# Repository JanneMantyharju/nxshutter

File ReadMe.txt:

This repository contains sources and schematics for Samsung NX camera remote shutter and rc interface
For more information see: http://wp.me/p12J9M-41

Files in this repository:
shutter/ - Source files, compile with arduino
shutter.sch - Schematics for camera cable
rx_switch.sch - Schematics for rc interface

The pin definitions are for AtTiny2313, change them if you use different type of
controller

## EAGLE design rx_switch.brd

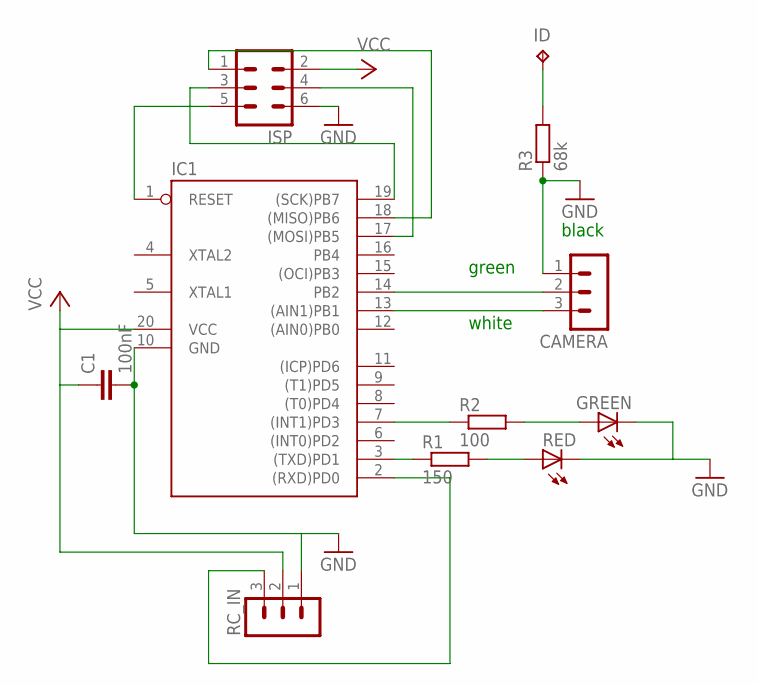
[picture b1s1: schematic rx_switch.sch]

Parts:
C1: 100nF; C0805
CAMERA: MA03-1
GREEN: LED_E; LED_1206
IC1: AT90S2313S; SO20L
ID: TPPAD1-13; P1-13
ISP: MA03-2
R1: 150; R1206
R2: 100; R1206
R3: 68k; R1206
RC_IN: MA03-1
RED: LED_E; LED_1206

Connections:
GND: C1.2, CAMERA.1, GREEN.C, IC1.10 (GND), ISP.6, R3.1, RC_IN.1, RED.C
ISP: IC1.19 ((SCK)PB7), ISP.3
unnamed: IC1.1 (RESET), ISP.5
unnamed: IC1.17 ((MOSI)PB5), ISP.4
unnamed: IC1.2 ((RXD)PD0), RC_IN.3
unnamed: CAMERA.2, IC1.14 (PB2)
unnamed: CAMERA.3, IC1.13 ((AIN1)PB1)
unnamed: IC1.18 ((MISO)PB6), ISP.1
unnamed: ID.TP, R3.2
unnamed: R1.2, RED.A
unnamed: IC1.7 ((INT1)PD3), R2.1
unnamed: IC1.3 ((TXD)PD1), R1.1
unnamed: GREEN.A, R2.2
VCC: C1.1, IC1.20 (VCC), ISP.2, RC_IN.2

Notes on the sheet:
black
green
white

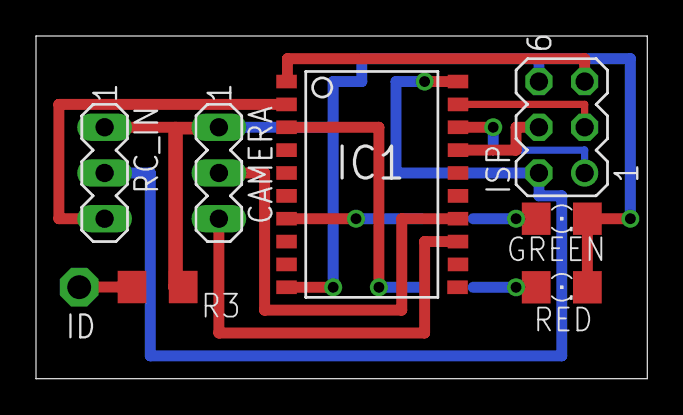
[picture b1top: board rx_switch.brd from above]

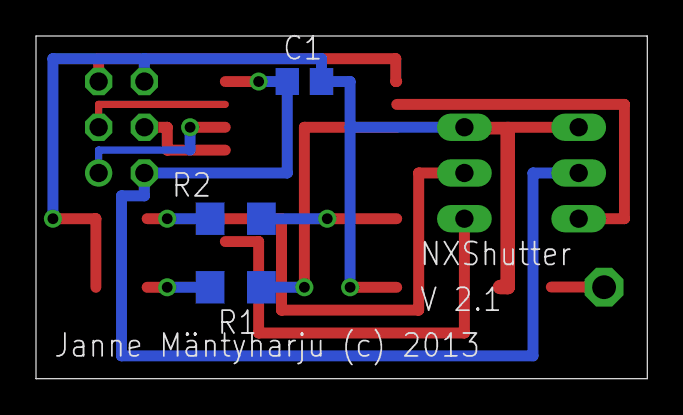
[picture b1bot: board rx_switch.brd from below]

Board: 2 copper layers, 34.0 x 19.0 mm, 11 parts (3 on the bottom side), 14 nets.

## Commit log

2013-10-03 Started creating pcb
2013-10-04 PCB design
2013-10-30 code changes
2013-10-31 PCB revision v.21
2015-09-20 Fixed NX500 / NX2000 support

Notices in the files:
rx_switch.brd:
Janne Mäntyharju (c) 2013
